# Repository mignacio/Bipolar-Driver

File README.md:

# Bipolar-Driver
L297-L298 bipolar stepper driver

This are the eagle files for a bipolar stepper driver using the L297-L298 IC pair.

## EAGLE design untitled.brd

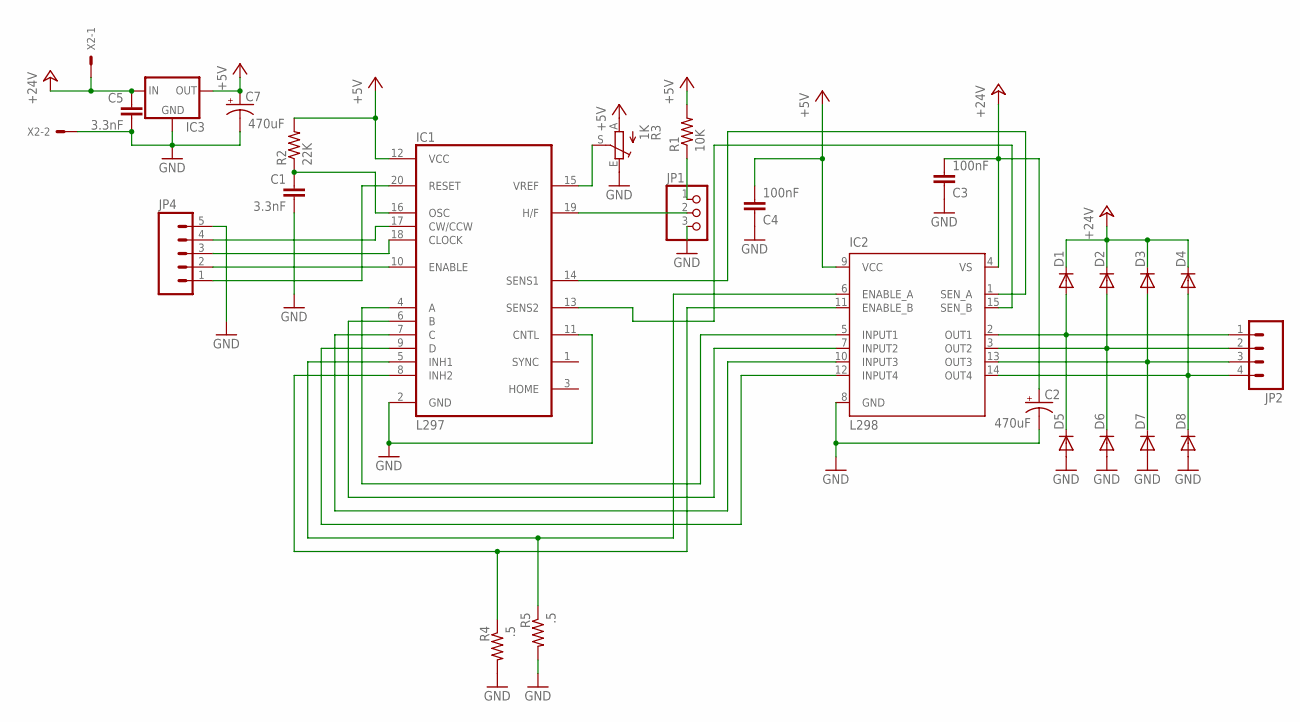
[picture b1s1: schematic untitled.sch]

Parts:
C1, C5: 3.3nF; C2.5-3
C2, C7: 470uF; CPOL-RADIAL-100UF-25V
C3, C4: 100nF; C2.5-3
D1, D2, D3, D4, D5, D6, D7, D8: DIODE-DO201-15; DO201-15
IC1: L297; DIL20
IC2: L298; MULTIWATT-15
IC3: V_REG_78XXSINK; TO220-IGO
JP1: PINHD-1X3; 1X03
JP2: M04PTH; 1X04
JP4: M05PTH; 1X05
R1: 10K; 0207/10
R2: 22K; 0207/10
R3: 1K; B64Y
R4, R5: .5; 0617/22
X2: KK-156-2

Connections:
+5V: C4.2, C7.1 (+), IC1.12 (VCC), IC2.9 (VCC), IC3.OUT, R1.2, R2.2, R3.A
+24V: C2.1 (+), C3.2, C5.1, D1.C, D2.C, D3.C, D4.C, IC2.4 (VS), IC3.IN, X2.1
GND: C1.2, C2.2 (-), C3.1, C4.1, C5.2, C7.2 (-), D5.A, D6.A, D7.A, D8.A, IC1.2 (GND), IC1.11 (CNTL), IC2.8 (GND), IC3.GND, JP1.3, JP4.5, R3.E, R4.2, R5.2, X2.2
unnamed: IC1.15 (VREF), R3.S
unnamed: JP1.1, R1.1
unnamed: D1.A, D5.C, IC2.2 (OUT1), JP2.1
unnamed: D2.A, D6.C, IC2.3 (OUT2), JP2.2
unnamed: IC1.5 (INH1), IC2.6 (ENABLE_A), R5.1
unnamed: IC1.8 (INH2), IC2.11 (ENABLE_B), R4.1
unnamed: IC1.19 (H/F), JP1.2
unnamed: IC1.13 (SENS2), IC2.15 (SEN_B)
unnamed: IC1.14 (SENS1), IC2.1 (SEN_A)
unnamed: IC1.10 (ENABLE), JP4.2
unnamed: IC1.18 (CLOCK), JP4.3
unnamed: IC1.17 (CW/CCW), JP4.4
unnamed: IC1.20 (RESET), JP4.1
unnamed: IC1.4 (A), IC2.5 (INPUT1)
unnamed: IC1.6 (B), IC2.7 (INPUT2)
unnamed: IC1.7 (C), IC2.10 (INPUT3)
unnamed: IC1.9 (D), IC2.12 (INPUT4)
unnamed: D3.A, D7.C, IC2.13 (OUT3), JP2.3
unnamed: D4.A, D8.C, IC2.14 (OUT4), JP2.4
unnamed: C1.1, IC1.16 (OSC), R2.1

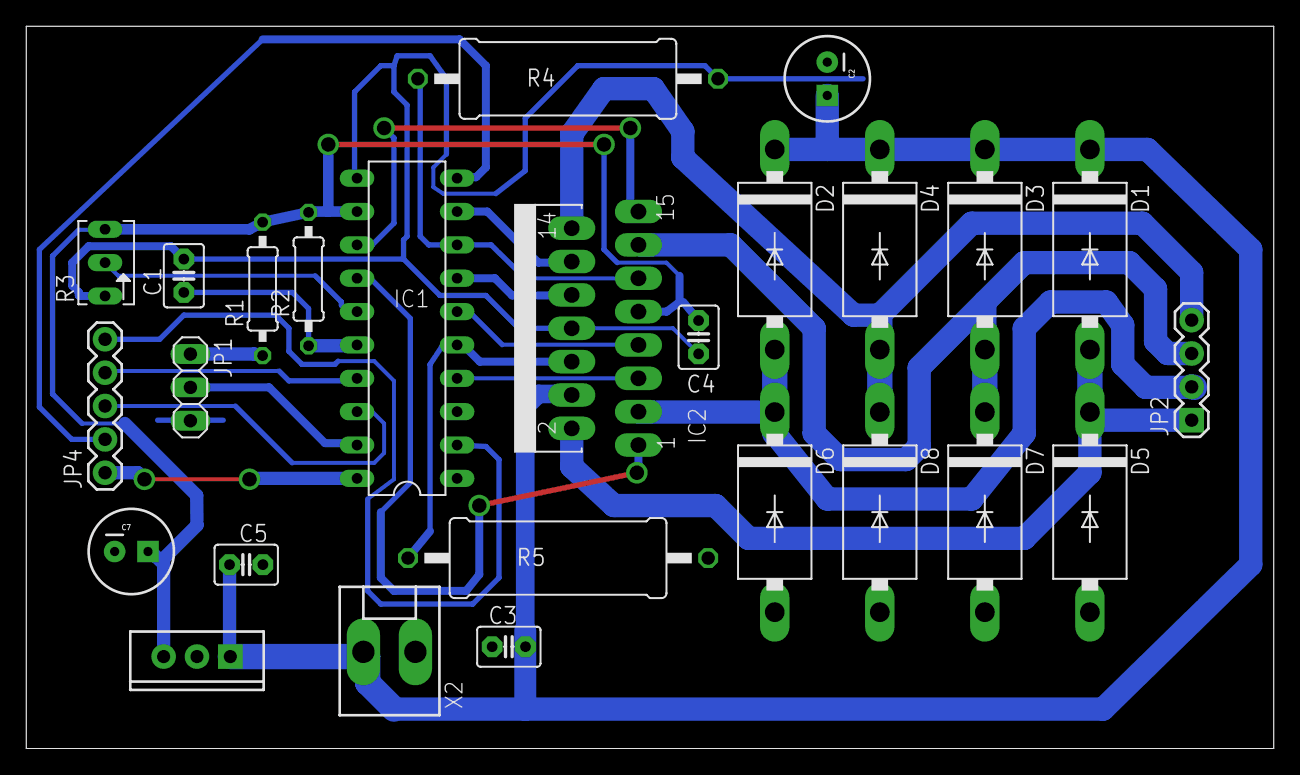
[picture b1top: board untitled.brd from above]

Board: 2 copper layers, 95.0 x 55.0 mm, 26 parts (0 on the bottom side), 23 nets.

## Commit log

2015-02-05 :lollipop: Added .gitattributes & .gitignore files
2015-02-05 Files added
2015-03-02 Another commit
2015-03-03 Nothing
2015-03-03 All traces routed
2015-03-05 Improved space between traces
2015-03-07 Se imprime
2015-03-14 Versión 2
2015-03-14 print PDF added

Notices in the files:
parts and their libraries:
SparkFun-PowerIC: Licensing: CC v3.0 Share-Alike You are welcome to use this library for commercial purposes.
SparkFun-Connectors: Licensing: Creative Commons ShareAlike 4.0 International - https://creativecommons.org/licenses/by-sa/4.0
